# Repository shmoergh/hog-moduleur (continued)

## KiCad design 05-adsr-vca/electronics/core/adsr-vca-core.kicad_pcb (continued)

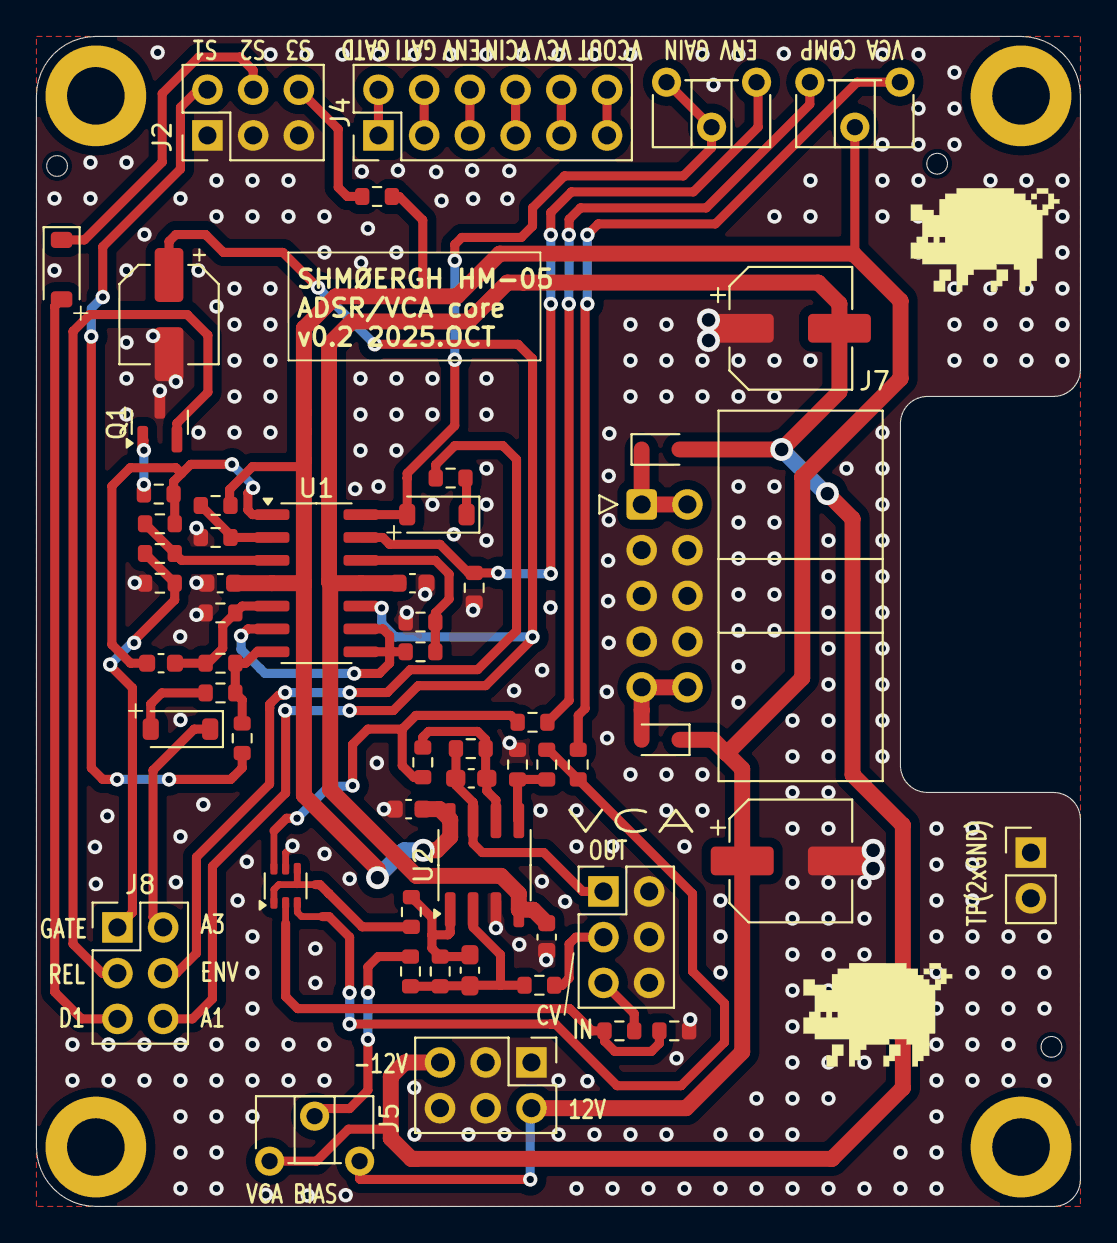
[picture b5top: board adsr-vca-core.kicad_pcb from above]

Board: 2 copper layers, 58.0 x 65.0 mm, 60 parts (0 on the bottom side), 46 nets.

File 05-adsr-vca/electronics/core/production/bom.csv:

Designator,Footprint,Quantity,Value,LCSC Part #
"C1, C2, C5, C6",0603,4,100n,C14663
"C10, C9",CP_Elec_6.3x7.7,2,100u,C2836437
C3,0603,1,10n,C57112
C4,CP_Elec_5x5.4,1,10u,C30110
"C7, C8",0603,2,47p,C1671
"D1, D2, D3",D_SOD-123,3,1N4148,C81598
"D4, D5",D_SOD-323,2,1N5817,C5190152
"J2, J3, J5, J8",PinHeader_2x03_P2.54mm_Vertical,4,Conn_02x03_Odd_Even,
J4,PinHeader_2x06_P2.54mm_Vertical,1,Conn_02x06_Odd_Even,
J6,PinHeader_1x02_P2.54mm_Vertical,1,Conn_01x02,
J7,IDC-Header_2x05_P2.54mm_Horizontal,1,Conn_02x05_Odd_Even,
Q1,SOT-23,1,BC857,C20069137
Q2,SOT-23,1,BC847,C7420337
Q3,SOT-363_SC-70-6,1,BC847BS,C5380687
R1,0603,1,22k,C31850
R10,R_Axial_DIN0207_L6.3mm_D2.5mm_P7.62mm_Horizontal,1,10k,
R11,R_Axial_DIN0207_L6.3mm_D2.5mm_P7.62mm_Horizontal,1,4.7k,
"R12, R23, R25, R26",0603,4,10k,C25804
R13,0603,1,15k,C22809
"R14, R15, R3",0603,3,47k,C25819
R16,R_Axial_DIN0207_L6.3mm_D2.5mm_P7.62mm_Horizontal,1,1k,
"R17, R2, R4, R9",0603,4,1k,C21190
"R18, R22, R24, R8",0603,4,100k,C25803
"R19, R29",0603,2,200k,C25811
R20,0603,1,220,C22962
R21,0603,1,33k,C4216
"R27, R28",0603,2,470k,C23178
"R5, R6, R7",0603,3,1M,C22935
RV_COMP1,"Potentiometer_ACP_CA6-H2,5_Horizontal",1,10k,
"RV_OUT_GAIN1, RV_VCA_BIAS1","Potentiometer_ACP_CA6-H2,5_Horizontal",2,100k,
U1,SOIC-14_3.9x8.7mm_P1.27mm,1,LM324,C71035
U2,SOIC-8_3.9x4.9mm_P1.27mm,1,TL072,C6961

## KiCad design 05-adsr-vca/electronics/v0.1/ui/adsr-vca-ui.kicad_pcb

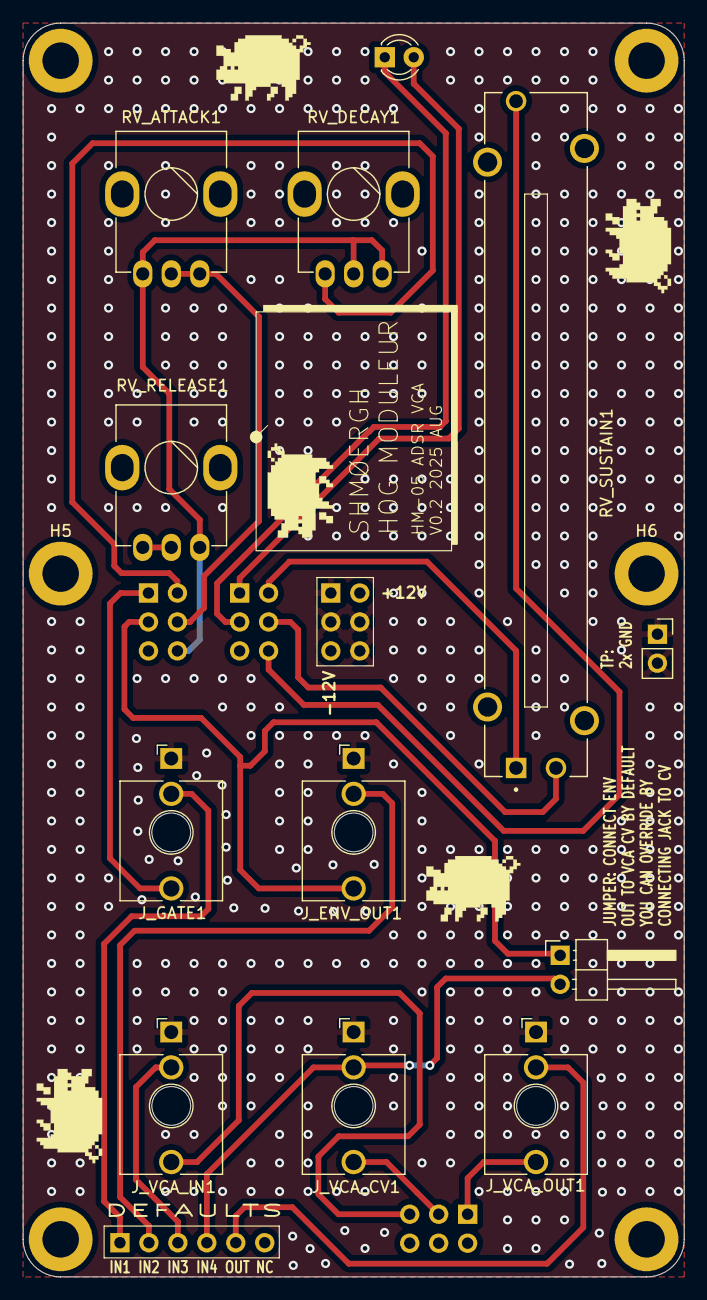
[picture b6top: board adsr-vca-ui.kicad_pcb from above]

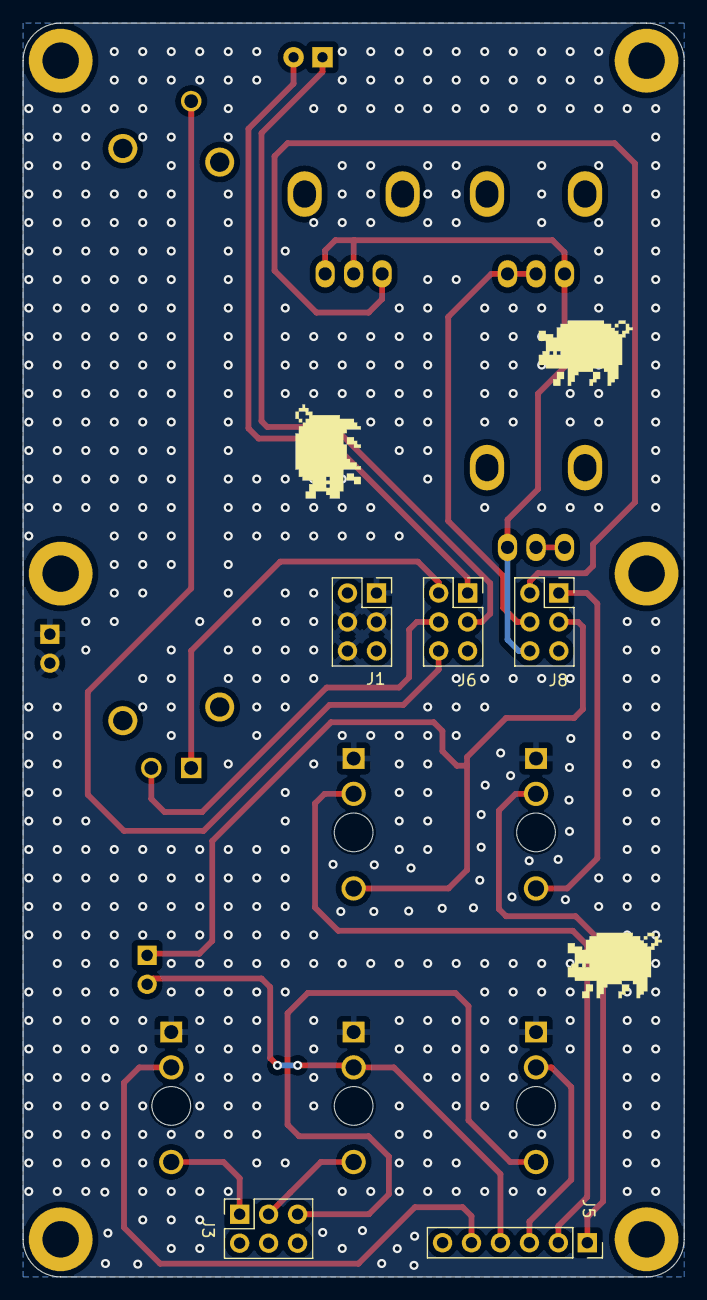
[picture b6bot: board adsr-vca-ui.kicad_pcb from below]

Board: 2 copper layers, 58.0 x 110.0 mm, 23 parts (5 on the bottom side), 20 nets.

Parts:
D1: D; LED_D3.0mm
H1, H2, H3, H4, H5, H6: MountingHole; MountingHole_3.2mm_M3_DIN965_Pad
J1, J3, J6, J8: Conn_02x03_Odd_Even; PinSocket_2x03_P2.54mm_Vertical
J4: Conn_01x02; PinSocket_1x02_P2.54mm_Vertical
J5: Conn_01x06; PinSocket_1x06_P2.54mm_Vertical
JP_DEFAULT_ENV_TO_VCA1: Jumper_2_Open; PinHeader_1x02_P2.54mm_Horizontal
J_ENV_OUT1: PJ398SM; Jack_3.5mm_QingPu_WQP-PJ398SM_Vertical_CircularHoles
J_GATE1: PJ398SM; Jack_3.5mm_QingPu_WQP-PJ398SM_Vertical_CircularHoles
J_VCA_CV1: PJ398SM; Jack_3.5mm_QingPu_WQP-PJ398SM_Vertical_CircularHoles
J_VCA_IN1: PJ398SM; Jack_3.5mm_QingPu_WQP-PJ398SM_Vertical_CircularHoles
J_VCA_OUT1: PJ398SM; Jack_3.5mm_QingPu_WQP-PJ398SM_Vertical_CircularHoles
RV_ATTACK1: A500k; Potentiometer_Bourns_Single-PTV09A
RV_DECAY1: A500k; Potentiometer_Bourns_Single-PTV09A
RV_RELEASE1: A500k; Potentiometer_Bourns_Single-PTV09A
RV_SUSTAIN1: 10k; TRIM_PTA4543-2015DPB103

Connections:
A1_D3_R3: J8.6, RV_ATTACK1.1, RV_DECAY1.2, RV_DECAY1.3, RV_RELEASE1.3
ATTACK_3: J8.4, RV_ATTACK1.2, RV_ATTACK1.3
DECAY_1: J8.2, RV_DECAY1.1
ENV_OUT: J8.3, JP_DEFAULT_ENV_TO_VCA1.1 (A), J_ENV_OUT1.T
ENV_OUT_DEFAULT: J5.2, J_ENV_OUT1.TN
GATE: J8.1, J_GATE1.T
GATE_DEFAULT: J5.1, J_GATE1.TN
GND: J1.1, J1.3, J1.4, J1.6, J4.1, J4.2, J_ENV_OUT1.S, J_GATE1.S, J_VCA_CV1.S, J_VCA_IN1.S, J_VCA_OUT1.S
LED_A: D1.2 (A), J6.1
LED_K: D1.1 (K), J6.3
RELEASE_1: RV_RELEASE1.1, RV_RELEASE1.2
SUSTAIN_1: J6.2, RV_SUSTAIN1.1
SUSTAIN_2: J6.4, RV_SUSTAIN1.2
SUSTAIN_3: J6.6, RV_SUSTAIN1.3
VCA_CV: J3.3, J_VCA_CV1.T
VCA_CV_DEFAULT: J5.4, JP_DEFAULT_ENV_TO_VCA1.2 (B), J_VCA_CV1.TN
VCA_IN: J3.5, J_VCA_IN1.T
VCA_IN_DEFAULT: J5.3, J_VCA_IN1.TN
VCA_OUT: J3.1, J_VCA_OUT1.T
VCA_OUT_DEFAULT: J5.5, J_VCA_OUT1.TN
